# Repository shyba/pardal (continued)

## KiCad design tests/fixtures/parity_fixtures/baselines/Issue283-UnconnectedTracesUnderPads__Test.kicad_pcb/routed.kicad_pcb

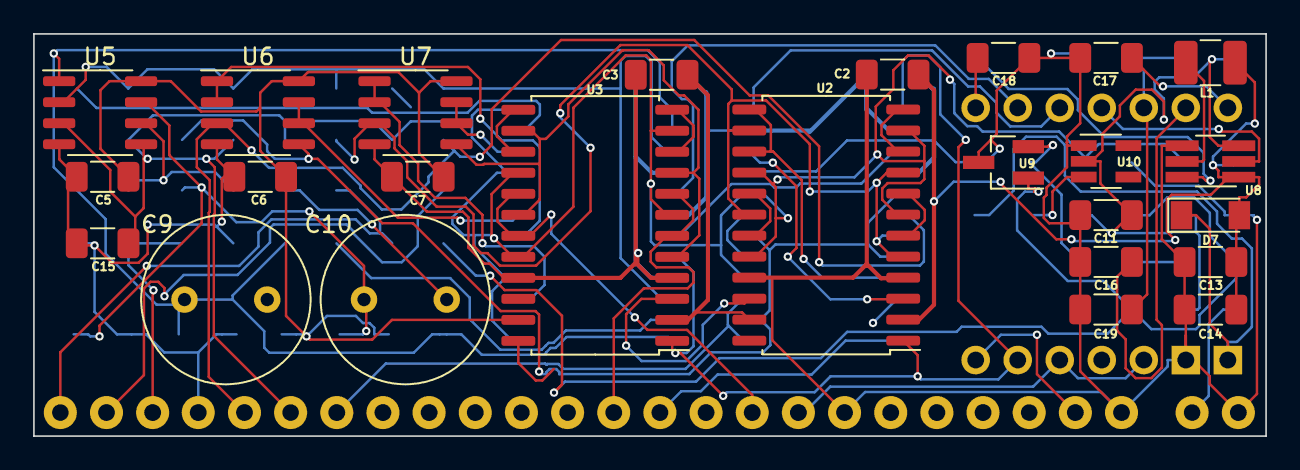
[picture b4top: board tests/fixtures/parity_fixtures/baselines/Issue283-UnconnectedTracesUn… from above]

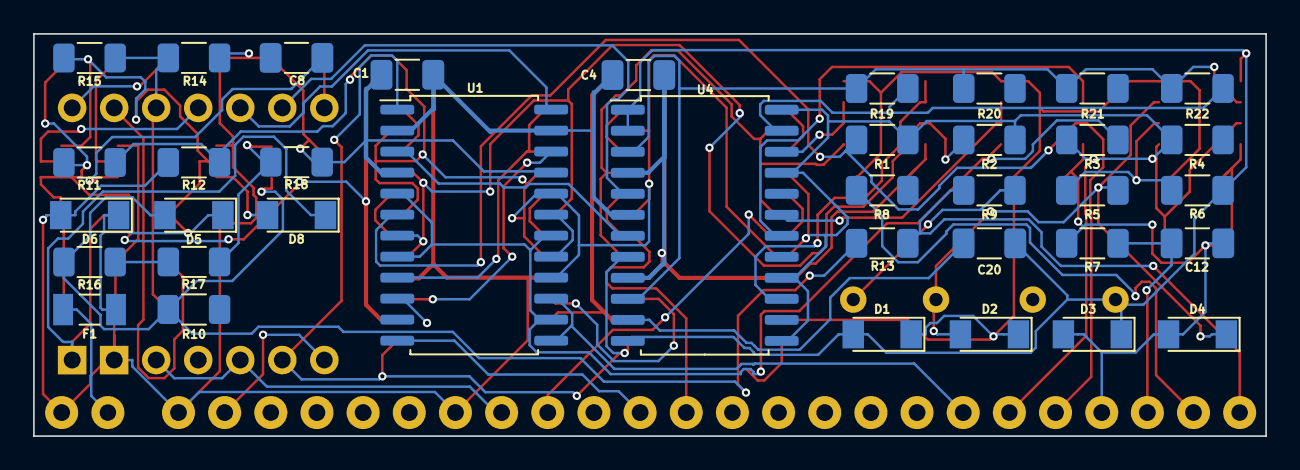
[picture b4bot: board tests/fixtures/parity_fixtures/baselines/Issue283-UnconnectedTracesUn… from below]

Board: 2 copper layers, 74.5 x 24.3 mm, 89 parts (37 on the bottom side), 57 nets.

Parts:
C1, C2, C3, C4, C5, C6, C7, C8, C12, C19: 0.1u; C_1206_3216Metric_Pad1.33x1.80mm_HandSolder
C9, C10: 47u; C_Radial_D10.0mm_H12.5mm_P5.00mm
C11: 10u; C_1206_3216Metric_Pad1.33x1.80mm_HandSolder
C13, C14, C15: 47u; C_1206_3216Metric_Pad1.33x1.80mm_HandSolder
C16, C17, C18, C20: 0.01u; C_1206_3216Metric_Pad1.33x1.80mm_HandSolder
D1, D2, D3, D4, D5, D6, D7, D8: LL4148; D_MiniMELF
F1: 0.1 A; Fuse_Bussman_1206_3216Metric_Pad1.42x1.75mm_HandSolder
J1: 1A+; SolderWirePad_1x01_Drill0.8mm
J2: 1A-; SolderWirePad_1x01_Drill0.8mm
J3: 1B+; SolderWirePad_1x01_Drill0.8mm
J4: 1B-; SolderWirePad_1x01_Drill0.8mm
J5: 2A+; SolderWirePad_1x01_Drill0.8mm
J6: 2A-; SolderWirePad_1x01_Drill0.8mm
J7: 2B+; SolderWirePad_1x01_Drill0.8mm
J8: 2B-; SolderWirePad_1x01_Drill0.8mm
J9: 3A+; SolderWirePad_1x01_Drill0.8mm
J10: 3A-; SolderWirePad_1x01_Drill0.8mm
J11: 3B+; SolderWirePad_1x01_Drill0.8mm
J12: 3B-; SolderWirePad_1x01_Drill0.8mm
J13: POT A; SolderWirePad_1x01_Drill0.8mm
J14: POT B; SolderWirePad_1x01_Drill0.8mm
J15: VOL W; SolderWirePad_1x01_Drill0.8mm
J16: PRE W; SolderWirePad_1x01_Drill0.8mm
J17: MOD W; SolderWirePad_1x01_Drill0.8mm
J18: LED +; SolderWirePad_1x01_Drill0.8mm
J19: LED D; SolderWirePad_1x01_Drill0.8mm
J20: LED -; SolderWirePad_1x01_Drill0.8mm
J21: OUT +; SolderWirePad_1x01_Drill0.8mm
J22: OUT -; SolderWirePad_1x01_Drill0.8mm
J23: OUT G; SolderWirePad_1x01_Drill0.8mm
J24: BAT +; SolderWirePad_1x01_Drill0.8mm
J25: BAT -; SolderWirePad_1x01_Drill0.8mm
J28: GND; SolderWirePad_1x01_Drill0.8mm
L1: 4.7u; L_1210_3225Metric_Pad1.42x2.65mm_HandSolder
R1, R2, R3, R4, R14: 1M; R_1206_3216Metric_Pad1.30x1.75mm_HandSolder
R5, R6: 47k; R_1206_3216Metric_Pad1.30x1.75mm_HandSolder
R7: 10; R_1206_3216Metric_Pad1.30x1.75mm_HandSolder
R8, R9: 100; R_1206_3216Metric_Pad1.30x1.75mm_HandSolder
R10, R13: 1K; R_1206_3216Metric_Pad1.30x1.75mm_HandSolder
R11, R12: 100k; R_1206_3216Metric_Pad1.30x1.75mm_HandSolder
R15: 10M; R_1206_3216Metric_Pad1.30x1.75mm_HandSolder
R16: 300k; R_1206_3216Metric_Pad1.30x1.75mm_HandSolder
R17: 10k; R_1206_3216Metric_Pad1.30x1.75mm_HandSolder
R18: 43k; R_1206_3216Metric_Pad1.30x1.75mm_HandSolder
R19, R20, R21, R22: 4k7; R_1206_3216Metric_Pad1.30x1.75mm_HandSolder
U1, U2, U3: MAX395CWG+; SOIC-24W_7.5x15.4mm_P1.27mm
U4: AD5206BRZ50; SOIC-24W_7.5x15.4mm_P1.27mm
U5, U6, U7: OPA2314/OPA2205/OPA1692; SOIC-8_3.9x4.9mm_P1.27mm
U8: AP63205WU; TSOT-23-6_HandSoldering
U9: ATL431; SOT-23_Handsoldering
U10: AP7383-44WR-7; SOT-23-5_HandSoldering
U11: SeeeduinoXIAO; Seeeduino_XIAO-MOUDLE14P-2.54-21X17.8MM_PINS

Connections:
+5V: C1.1, C2.1, C3.1, C4.1, C5.1, C6.1, C7.1, C13.1, C14.1, D1.1 (K), D2.1 (K), D7.2 (A), J18.1, L1.2, R11.1, U1.2 (V+), U1.23 (*RESET), U2.2 (V+), U2.23 (*RESET), U3.2 (V+), U3.23 (*RESET), U4.6 (VDD), U5.8 (V+), U6.8 (V+), U7.8 (V+), U8.1 (FB)
GND: C1.2, C2.2, C3.2, C4.2, C5.2, C6.2, C7.2, C11.2, C12.1, C13.2, C14.2, C15.2, C16.2, C17.2, C18.2, C19.2, D3.2 (A), D4.2 (A), D6.2 (A), J14.1, J20.1, J25.1, J28.1, R7.1, R12.2, R14.2, R18.2, U1.4 (GND), U1.21 (V-), U2.4 (GND), U2.21 (V-), U3.4 (GND), U3.21 (V-), U4.4 (GND), U4.9 (VSS), U5.4 (V-), U6.4 (V-), U7.4 (V-), U8.4 (GND), U9.3 (A), U10.1 (GND), U11.13 (GND)
unnamed: C8.1, U8.6 (BST)
unnamed: C8.2, L1.1, U8.5 (SW)
unnamed: C9.2, R8.1
unnamed: C10.1, D2.2 (A), D4.1 (K), R5.1, U5.7 (OUTB)
unnamed: C10.2, R9.1
unnamed: C11.1, D5.1 (K), D6.1 (K), F1.1, R15.2, U8.3 (IN), U10.2 (VIN)
unnamed: C12.2, J23.1, R7.2
unnamed: C15.1, J2.1, R1.1, R2.1, R3.2, R4.2, R11.2, R12.1, U1.16 (NO5), U1.20 (NO7), U2.7 (NO1), U2.11 (NO3), U2.16 (NO5), U2.20 (NO7), U3.7 (NO1), U3.11 (NO3), U3.16 (NO5), U3.20 (NO7), U4.13 (B3), U4.16 (B1), U4.21 (B2), U4.24 (B4), U5.3 (+INA), U5.5 (+INB)
unnamed: C16.1, J16.1, U11.2 (PA4_A1_D1)
unnamed: C17.1, J15.1, U11.1 (PA02_A0_D0)
unnamed: C18.1, J17.1, U11.7 (PB08_A6_D6_TX)
unnamed: C19.1, R14.1, R15.1, U11.3 (PA10_A2_D2)
unnamed: C9.1, C20.1, D1.2 (A), D3.1 (K), R6.2, U4.1 (A6), U4.2 (W6), U4.12 (A5), U5.1 (OUTA)
unnamed: C20.2, U4.11 (W5)
unnamed: D5.2 (A), R10.2, R13.1, R16.1, U9.1 (K)
unnamed: D7.1 (K), D8.1 (K), U11.14 (5V)
unnamed: D8.2 (A), U10.3 (VOUT)
unnamed: F1.2, J24.1
unnamed: J1.1, R1.2, U1.6 (COM0), U6.3 (+INA)
unnamed: J3.1, U1.13 (COM4), U1.15 (COM5)
unnamed: J4.1, U1.17 (COM6), U1.19 (COM7)
unnamed: J5.1, U2.6 (COM0), U2.8 (COM1)
unnamed: J6.1, U1.10 (COM2), U2.10 (COM2), U2.12 (COM3)
unnamed: J7.1, U1.9 (NO2), U2.13 (COM4), U2.15 (COM5)
unnamed: J8.1, U2.17 (COM6), U2.19 (COM7)
unnamed: J9.1, U3.6 (COM0), U3.8 (COM1)
unnamed: J10.1, U1.12 (COM3), U3.10 (COM2), U3.12 (COM3)
unnamed: J11.1, U1.11 (NO3), U3.13 (COM4), U3.15 (COM5)
unnamed: J12.1, U3.17 (COM6), U3.19 (COM7)
unnamed: J13.1, U11.10 (PA5_A9_D9_MISO), U11.12 (3V3)
unnamed: J19.1, U11.8 (PB09_A7_D7_RX)
unnamed: J21.1, R9.2, R13.2
unnamed: J22.1, R8.2, R10.1
unnamed: R2.2, U1.7 (NO1), U2.5 (NO0), U2.9 (NO2), U2.14 (NO4), U2.18 (NO6), U7.3 (+INA)
unnamed: R3.1, U1.5 (NO0), U1.8 (COM1), U1.14 (NO4), U1.18 (NO6), U6.5 (+INB)
unnamed: R4.1, U3.5 (NO0), U3.9 (NO2), U3.14 (NO4), U3.18 (NO6), U7.5 (+INB)
unnamed: R5.2, R6.1, U5.6 (-INB)
unnamed: R16.2, R17.1
unnamed: R17.2, R18.1, U9.2 (REF)
unnamed: R19.1, U4.17 (W1)
unnamed: R19.2, R20.2, R21.2, R22.2, U4.3 (B6), U4.10 (B5), U5.2 (-INA)
unnamed: R20.1, U4.20 (W2)
unnamed: R21.1, U4.14 (W3)
unnamed: R22.1, U4.23 (W4)
unnamed: U1.1 (SCLK), U2.1 (SCLK), U3.1 (SCLK), U4.8 (CLK), U11.9 (PA7_A8_D8_SCK)
unnamed: U1.3 (DIN), U4.7 (SDI), U11.11 (PA6_A10_D10_MOSI)
unnamed: U1.22 (DOUT), U2.3 (DIN)
unnamed: U1.24 (*CS), U2.24 (*CS), U3.24 (*CS), U11.5 (PA8_A4_D4_SDA)
unnamed: U2.22 (DOUT), U3.3 (DIN)
unnamed: U4.15 (A3), U7.1 (OUTA), U7.2 (-INA)
unnamed: U4.18 (A1), U6.1 (OUTA), U6.2 (-INA)
unnamed: U4.19 (A2), U6.6 (-INB), U6.7 (OUTB)
unnamed: U4.22 (A4), U7.6 (-INB), U7.7 (OUTB)
unnamed: U8.2 (EN), U11.4 (PA11_A3_D3)
unnamed: U4.5 (CS*), U11.6 (PA9_A5_D5_SCL)

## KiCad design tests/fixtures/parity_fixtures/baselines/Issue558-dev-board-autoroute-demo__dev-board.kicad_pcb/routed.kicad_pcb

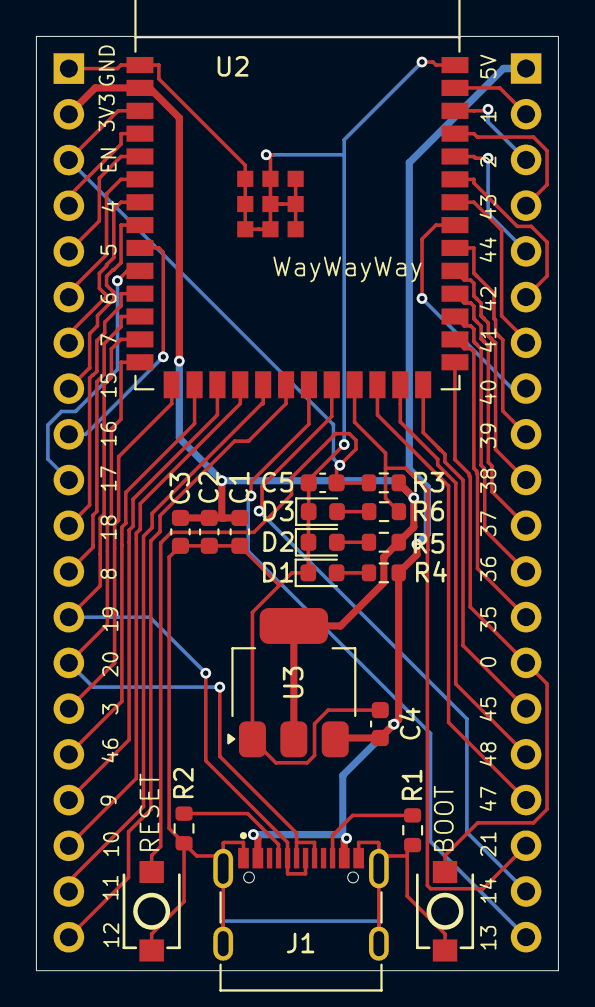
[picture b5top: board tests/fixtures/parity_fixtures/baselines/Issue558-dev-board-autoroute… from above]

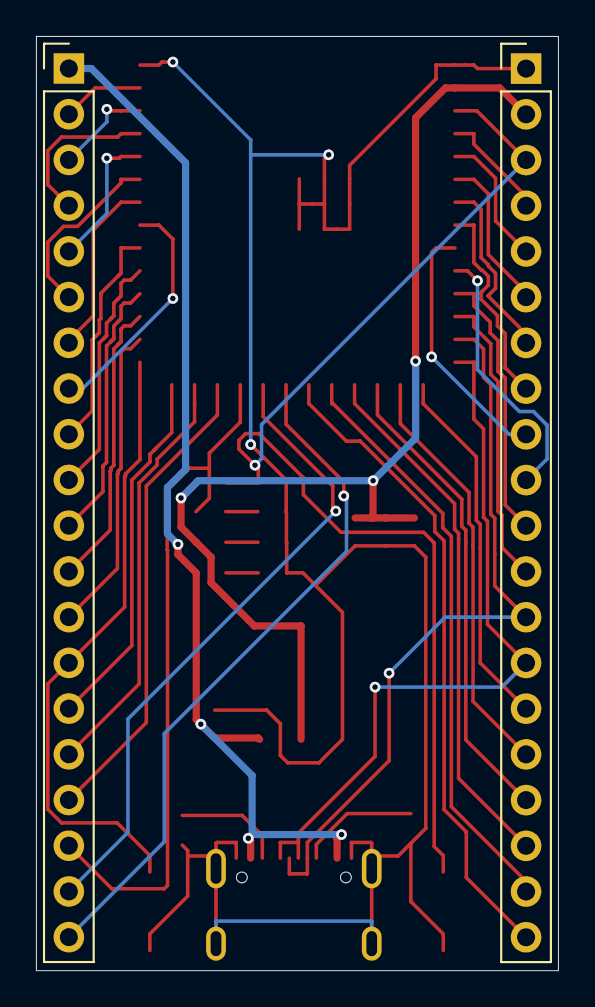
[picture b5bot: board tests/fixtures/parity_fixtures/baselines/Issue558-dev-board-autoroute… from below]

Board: 2 copper layers, 29.0 x 51.9 mm, 21 parts (2 on the bottom side), 45 nets.

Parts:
C1, C4, C5: 10u; C_0603_1608Metric
C2: 22u; C_0603_1608Metric
C3: 100n; C_0603_1608Metric
D1: RED; LED_0603_1608Metric
D2: GREEN; LED_0603_1608Metric
D3: BLUE; LED_0603_1608Metric
J1: TYPE-C-31-M-12; HRO_TYPE-C-31-M-12
J2, J3: Conn_01x20_Pin; PinHeader_1x20_P2.54mm_Vertical
R1, R2, R3, R4, R5, R6: 5.1K; R_0603_1608Metric
SW1, SW2: TS-1088-AR02016; SW-SMD_L3.9-W3.0-P4.45
U2: ESP32-S3-WROOM-1
U3: LD1117S33TR_SOT223; SOT-223-3_TabPin2

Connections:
+3V3: C1.1, C2.1, C3.1, J2.2, R3.1, R5.1, U2.2 (3V3), U3.2 (VO)
+5V: C4.1, J1.A4_B9 (VBUS), J1.B4_A9 (VBUS), J3.1, R4.1, U3.3 (VI)
D+: J1.A6 (DP1), J1.B6 (DP2), J2.14, U2.14 (GPIO20/U1CTS/ADC2_CH9/CLK_OUT1/USB_D+)
D-: J1.A7 (DN1), J1.B7 (DN2), J2.13, U2.13 (GPIO19/U1RTS/ADC2_CH8/CLK_OUT2/USB_D-)
EN: C5.1, J2.3, R3.2, SW1.2, U2.3 (EN)
GND: C1.2, C2.2, C3.2, C4.2, C5.2, D1.1 (K), D2.1 (K), D3.1 (K), J1.A1_B12 (GND), J1.B1_A12 (GND), J1.S1 (SHIELD), J1.S2 (SHIELD), J1.S3 (SHIELD), J1.S4 (SHIELD), J2.1, R1.2, R2.2, SW1.1, SW2.1, U2.1 (GND), U2.40 (GND), U2.41 (GND), U3.1 (GND)
GPIO0: J3.14, SW2.2, U2.27 (GPIO0/BOOT)
GPIO1: J3.2, U2.39 (GPIO1/TOUCH1/ADC1_CH0)
GPIO2: J3.3, U2.38 (GPIO2/TOUCH2/ADC1_CH1)
GPIO3: J2.15, U2.15 (GPIO3/TOUCH3/ADC1_CH2)
GPIO4: J2.4, U2.4 (GPIO4/TOUCH4/ADC1_CH3)
GPIO5: J2.5, U2.5 (GPIO5/TOUCH5/ADC1_CH4)
GPIO6: J2.6, U2.6 (GPIO6/TOUCH6/ADC1_CH5)
GPIO7: J2.7, U2.7 (GPIO7/TOUCH7/ADC1_CH6)
GPIO8: J2.12, U2.12 (GPIO8/TOUCH8/ADC1_CH7/SUBSPICS1)
GPIO9: J2.17, U2.17 (GPIO9/TOUCH9/ADC1_CH8/FSPIHD/SUBSPIHD)
GPIO10: J2.18, U2.18 (GPIO10/TOUCH10/ADC1_CH9/FSPICS0/FSPIIO4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)
GPIO11: J2.19, U2.19 (GPIO11/TOUCH11/ADC2_CH0/FSPID/FSPIIO5/S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)
GPIO12: J2.20, U2.20 (GPIO12/TOUCH12/ADC2_CH1/FSPICLK/FSPIIO6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)
GPIO13: J3.20, U2.21 (GPIO13/TOUCH13/ADC2_CH2/FSPIQ/FSPIIO7/S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)
GPIO14: J3.19, U2.22 (GPIO14/TOUCH14/ADC2_CH3/FSPIWP/FSPIDQS/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)
GPIO15: J2.8, U2.8 (GPIO15/U0RTS/ADC2_CH4/XTAL_32K_P)
GPIO16: J2.9, U2.9 (GPIO16/U0CTS/ADC2_CH5/XTAL_32K_N)
GPIO17: J2.10, U2.10 (GPIO17/U1TXD/ADC2_CH6)
GPIO18: J2.11, U2.11 (GPIO18/U1RXD/ADC2_CH7/CLK_OUT3)
GPIO21: J3.18, R6.1, U2.23 (GPIO21)
GPIO35: J3.13, U2.28 (SPIIO6/GPIO35/FSPID/SUBSPID)
GPIO36: J3.12, U2.29 (SPIIO7/GPIO36/FSPICLK/SUBSPICLK)
GPIO37: J3.11, U2.30 (SPIDQS/GPIO37/FSPIQ/SUBSPIQ)
GPIO38: J3.10, U2.31 (GPIO38/FSPIWP/SUBSPIWP)
GPIO39: J3.9, U2.32 (MTCK/GPIO39/CLK_OUT3/SUBSPICS1)
GPIO40: J3.8, U2.33 (MTDO/GPIO40/CLK_OUT2)
GPIO41: J3.7, U2.34 (MTDI/GPIO41/CLK_OUT1)
GPIO42: J3.6, U2.35 (MTMS/GPIO42)
GPIO43: J3.4, U2.37 (U0TXD/GPIO43/CLK_OUT1)
GPIO44: J3.5, U2.36 (U0RXD/GPIO44/CLK_OUT2)
GPIO45: J3.15, U2.26 (GPIO45)
GPIO46: J2.16, U2.16 (GPIO46)
GPIO47: J3.17, U2.24 (GPIO47/SPICLK_P/SUBSPICLK_P_DIFF)
GPIO48: J3.16, U2.25 (GPIO48/SPICLK_N/SUBSPICLK_N_DIFF)
unnamed: D1.2 (A), R4.2
unnamed: D2.2 (A), R5.2
unnamed: D3.2 (A), R6.2
unnamed: J1.A5 (CC1), R2.1
unnamed: J1.B5 (CC2), R1.1

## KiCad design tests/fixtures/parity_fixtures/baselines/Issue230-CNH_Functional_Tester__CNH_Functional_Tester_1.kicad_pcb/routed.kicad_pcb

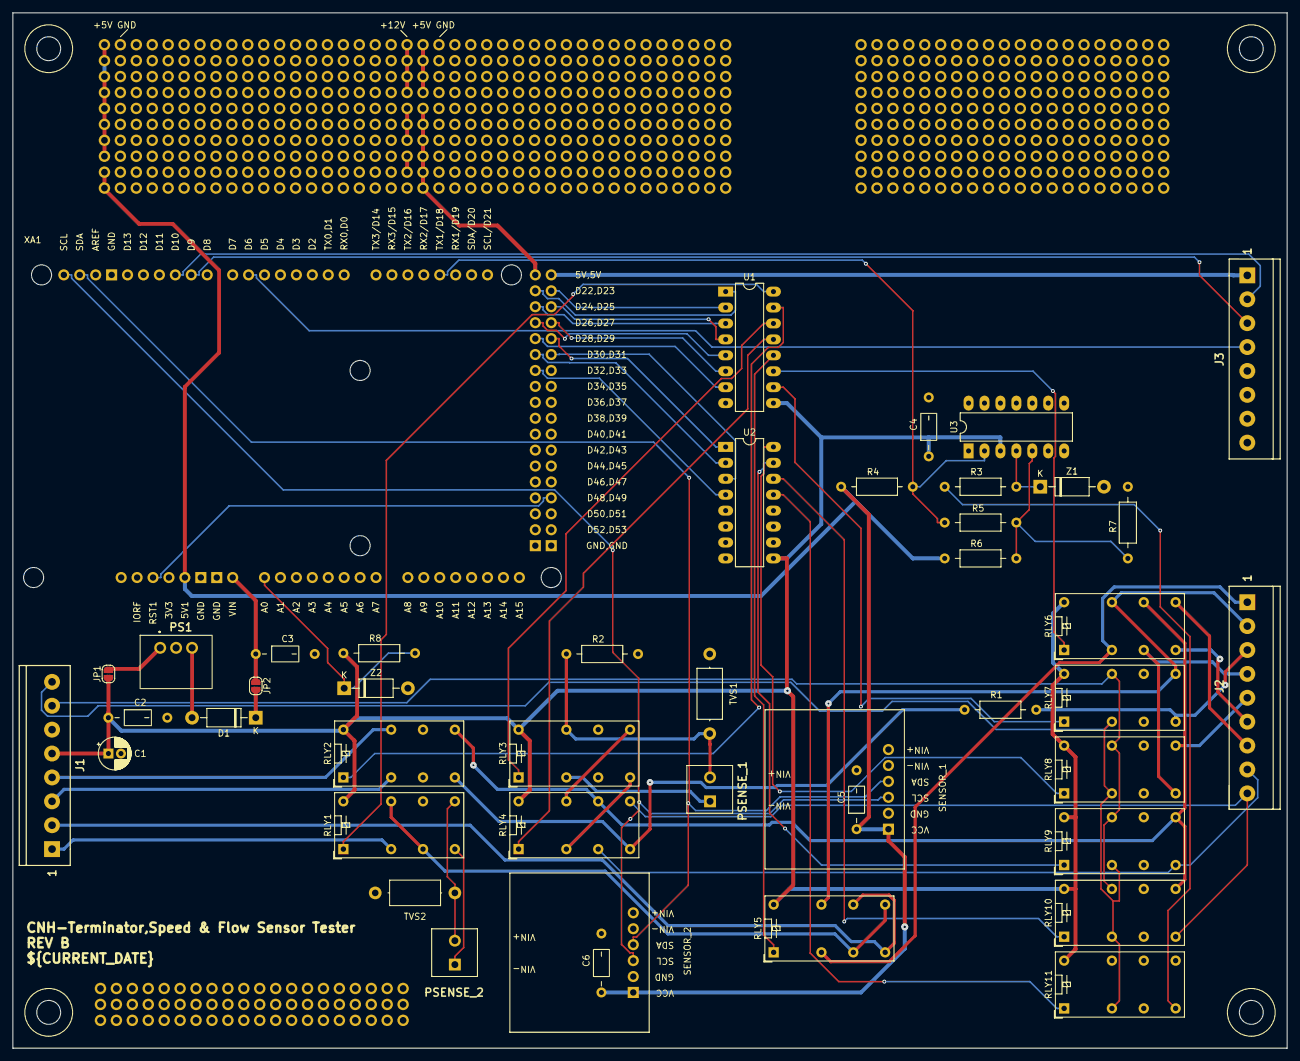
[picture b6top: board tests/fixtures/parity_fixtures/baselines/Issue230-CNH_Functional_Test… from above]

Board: 4 copper layers, 203.2 x 165.1 mm, 81 parts (0 on the bottom side), 64 nets.

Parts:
C1: 10uF 35v; CP_Radial_D5.0mm_P2.00mm
C2, C3, C4, C5, C6: 0.1uF; C_Axial_L170mil_D100mil_P370mil_Horizontal
D1: 1N5817; D_DO-41_SOD81_P10.16mm_Horizontal
J1, J3: EDSTLZ1555_8; CONN-TH_EDSTLZ1555-8
J2: EDSTLZ1555_9; CONN-TH_EDSTLZ1555-9
JP1, JP2: SolderJumper_2_Open; SolderJumper-2_P1.3mm_Open_RoundedPad1.0x1.5mm
MTH1, MTH2, MTH3, MTH4: MTH 6-32_NPTH
PR1, PR2, PR3, PR4, PR5, PR6, PR7, PR8, PR9, PR10, PR11, PR12, PR13, PR14, PR15, PR16, PR17, PR18, PR19, PR20, PR21, PR22, PR23, PR24, PR25, PR26, PR27, PR28, PR29, PR30, PR31, PR32, PR33: Conn_01x20_Perf; SIP-20_PERF
PS1: R-78B_9.0V-1.0A; R78_9V_1A_SIP_TH
PSENSE_1, PSENSE_2: 1727010_2PIN_3.81mm_CONN
R1: 1k 1/2W; R_Axial_DIN0207_L6.3mm_D2.5mm_P11.43mm_Horizontal_0.25W
R2: 5.6k; R_Axial_DIN0207_L6.3mm_D2.5mm_P11.43mm_Horizontal_0.25W
R3, R6, R8: 1K; R_Axial_DIN0207_L6.3mm_D2.5mm_P11.43mm_Horizontal_0.25W
R4: 10K; R_Axial_DIN0207_L6.3mm_D2.5mm_P11.43mm_Horizontal_0.25W
R5: 33K; R_Axial_DIN0207_L6.3mm_D2.5mm_P11.43mm_Horizontal_0.25W
R7: 2K; R_Axial_DIN0207_L6.3mm_D2.5mm_P11.43mm_Horizontal_0.25W
RLY1, RLY2, RLY3, RLY4, RLY5, RLY6, RLY7, RLY8, RLY9, RLY10, RLY11: G5V-2_12DC; Relay_DPDT_Omron_G5V-2
SENSOR_1, SENSOR_2: INA219_CURRENT_SENSOR
TVS1, TVS2: SA20CA; SA20CA_P12.70mm_Horizontal
U1, U2: ULN2003A; DIP-16_W7.62mm_LongPads
U3: LM339; DIP-14_W7.62mm_LongPads
XA1: Arduino_Mega2560_Shield
Z1, Z2: 1N4732A; D_DO-41_SOD81_P10.16mm_Horizontal

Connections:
+5V: C5.1, C6.1, PR1.20, PR2.20, PR3.20, PR4.20, PR5.20, PR6.20, PR7.20, PR8.20, PR9.20, PR10.20, PR11.20, PR12.20, PR13.20, PR14.20, PR15.20, PR16.20, PR17.20, PR18.20, PR19.20, PR20.20, R4.1, R6.1, SENSOR_1.1 (VCC), SENSOR_2.1 (VCC), XA1.5V1 (5V), XA1.5V3 (5V)
+5VP: J3.1, XA1.5V4 (5V)
+12V: C1.1, C2.1, C4.1, J1.5, JP1.1 (A), PR1.1, PR2.1, PR3.1, PR4.1, PR5.1, PR6.1, PR7.1, PR8.1, PR9.1, PR10.1, R8.1, RLY1.16, RLY2.16, RLY3.16, RLY4.16, RLY5.16, RLY6.16, RLY7.16, RLY8.16, RLY9.16, RLY10.16, RLY11.16, U1.9 (COM), U2.9 (COM), U3.3 (V+)
/9DIO: D1.1 (K), JP2.2 (B)
/9OUT: D1.2 (A), PS1.3 (+VOUT)
/12IN: JP1.2 (B), PS1.1 (+VIN)
/+SCOPE_CH1: J1.8, RLY7.4, RLY8.4, RLY9.4, RLY10.4, RLY11.4
/+VDC_LOAD: J1.3, RLY2.4
/+VDC_UUT: RLY1.6, RLY1.13, RLY5.6, RLY5.9
/+VDC_UUT_MAIN: J1.1, RLY1.4
/+VL_SW: R1.1, RLY2.8, RLY4.8
/-SCOPE_CH1: J1.7, RLY7.13, RLY8.13, RLY9.13, RLY10.13
/-VDC_LOAD: J1.4, RLY2.13
/-VDC_UUT_MAIN: J1.2, RLY5.8, RLY5.11
/CAN_BAT: J2.4, RLY6.6, RLY8.8
/CAN_GND: J2.5, RLY2.9, RLY4.11, RLY6.11, RLY8.9, RLY9.9, RLY10.9
/CAN_H: J2.9, RLY4.9, RLY10.8
/CAN_L: J2.8, RLY4.6, RLY9.8
/DIR-: J3.3, XA1.D9
/ENA-: J3.2, XA1.D10
/PUL-: J3.4, XA1.D6
/PULSE_COUNT: R4.2, R5.2, U3.2, XA1.D18 (D18_TX1)
/PWR_ON: R8.2, XA1.A0, Z2.1
/RLY1: RLY1.1, U1.16 (O1)
/RLY2: RLY2.1, U1.15 (O2)
/RLY3: RLY3.1, U1.14 (O3)
/RLY4: RLY4.1, U1.13 (O4)
/RLY5: RLY5.1, U1.12 (O5)
/RLY6: RLY6.1, U1.11 (O6)
/RLY7: RLY7.1, U1.10 (O7)
/RLY8: RLY8.1, U2.16 (O1)
/RLY9: RLY9.1, U2.15 (O2)
/RLY10: RLY10.1, U2.14 (O3)
/RLY11: RLY11.1, U2.13 (O4)
/SCL: SENSOR_1.3 (SCL), SENSOR_2.3 (SCL), XA1.SCL
/SDA: SENSOR_1.4 (SDA), SENSOR_2.4 (SDA), XA1.SDA
/SIG_GND: J2.2, RLY5.13, RLY6.13, RLY7.9
/UUT_IN+: J2.1, RLY5.4, RLY6.4
/Vin_Atmega: C3.1, JP2.1 (A), XA1.VIN
GND: C1.2, C2.2, C3.2, C4.2, C5.2, C6.2, J1.6, PR1.19, PR2.19, PR3.19, PR4.19, PR5.19, PR6.19, PR7.19, PR8.19, PR9.19, PR10.19, PR11.19, PR12.19, PR13.19, PR14.19, PR15.19, PR16.19, PR17.19, PR18.19, PR19.19, PR20.19, PS1.2 (GND), R2.2, R7.2, SENSOR_1.2 (GND), SENSOR_2.2 (GND), TVS1.1 (A1), TVS2.2 (A2), U1.8 (GND), U2.8 (GND), U3.6 (-), U3.7 (+), U3.8 (-), U3.9 (+), U3.10 (-), U3.11 (+), U3.12 (V-), XA1.GND1 (GND), XA1.GND2 (GND), XA1.GND3 (GND), XA1.GND5 (GND), XA1.GND6 (GND), Z1.2, Z2.2
unnamed: J2.3, R1.2, RLY7.8
unnamed: J2.6, RLY6.8
unnamed: J2.7, RLY6.9
unnamed: PSENSE_1.1, RLY3.4
unnamed: PSENSE_2.1, RLY1.8
unnamed: R3.1, RLY11.8
unnamed: RLY3.8, RLY4.4
unnamed: RLY3.9, RLY4.13
unnamed: PSENSE_1.2, R2.1, RLY3.13, TVS1.2 (A2)
unnamed: PSENSE_2.2, RLY1.9, TVS2.1 (A1)
unnamed: U1.1 (I1), XA1.D22
unnamed: U1.2 (I2), XA1.D23
unnamed: U1.3 (I3), XA1.D24
unnamed: U1.4 (I4), XA1.D25
unnamed: U1.5 (I5), XA1.D26
unnamed: U1.6 (I6), XA1.D27
unnamed: U1.7 (I7), XA1.D28
unnamed: U2.1 (I1), XA1.D29
unnamed: U2.2 (I2), XA1.D30
unnamed: U2.3 (I3), XA1.D31
unnamed: U2.4 (I4), XA1.D32
unnamed: R5.1, R6.2, R7.1, U3.5 (+)
unnamed: R3.2, U3.4 (-), Z1.1
unnamed: XA1.D49, XA1.RST1 (RESET)

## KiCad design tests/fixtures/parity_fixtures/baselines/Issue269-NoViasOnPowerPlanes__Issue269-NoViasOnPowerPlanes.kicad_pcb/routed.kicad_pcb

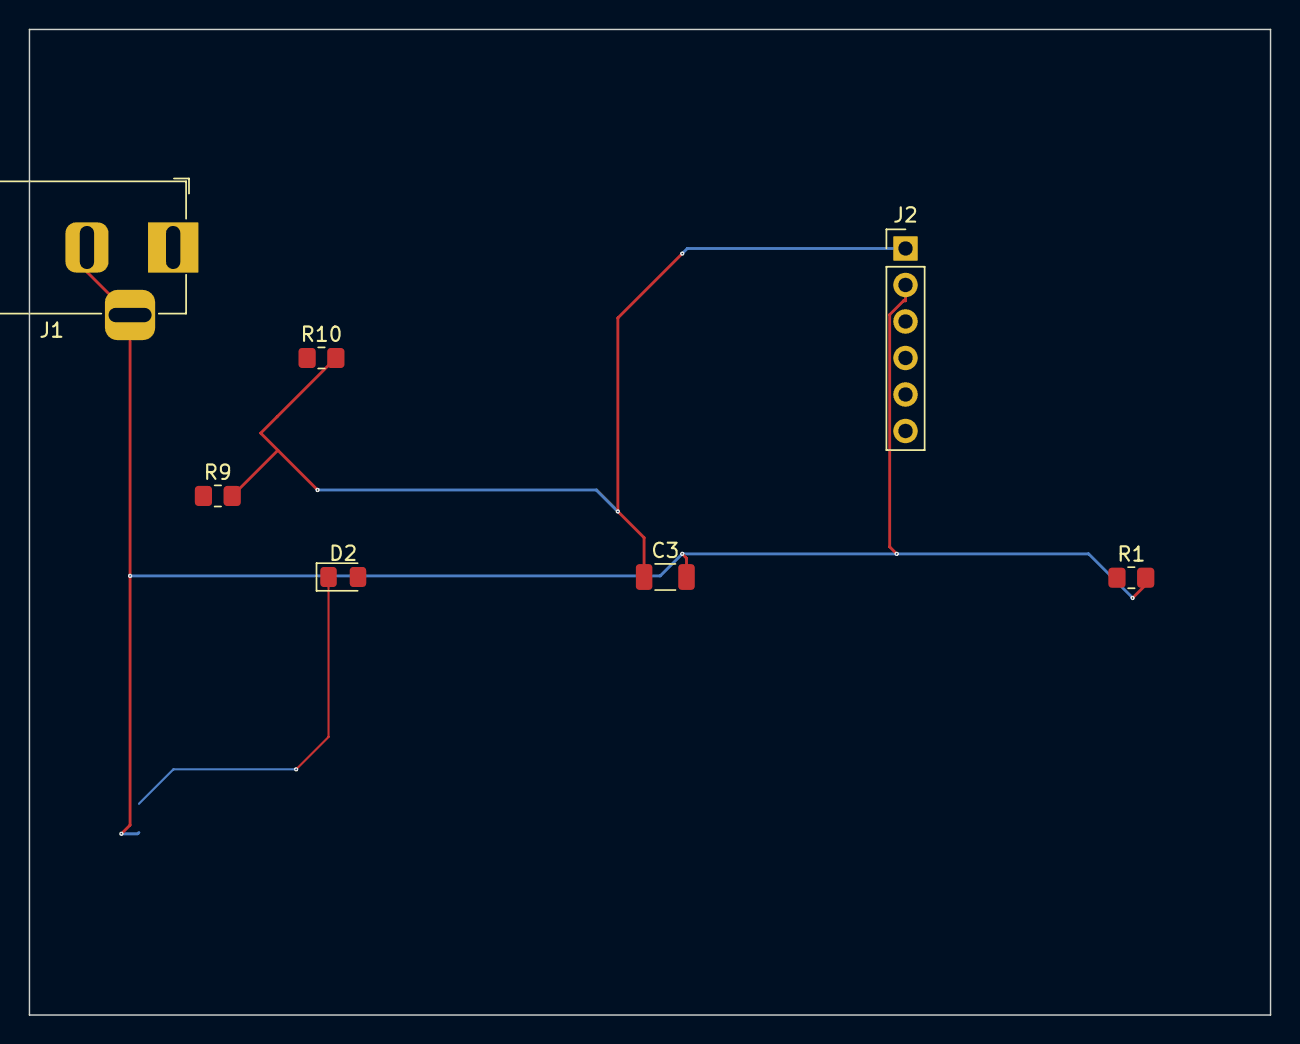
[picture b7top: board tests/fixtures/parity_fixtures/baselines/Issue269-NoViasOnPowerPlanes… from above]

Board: 4 copper layers, 86.4 x 68.6 mm, 8 parts (1 on the bottom side), 3 nets.

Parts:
C3: 100n; C_1206_3216Metric
D2: LED; LED_0805_2012Metric_Pad1.15x1.40mm_HandSolder
J1: Barrel_Jack_Switch; BarrelJack_Horizontal
J2: Conn_01x06; PinHeader_1x06_P2.54mm_Vertical
R1, R6, R9, R10: 4.7k; R_0805_2012Metric_Pad1.20x1.40mm_HandSolder

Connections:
+3V3: C3.1, J2.1, R9.2, R10.2
/FPGA_DONE: D2.1 (K), R6.2
GNDREF: C3.2, J1.2, J1.3, J2.2, R1.2, R6.1
